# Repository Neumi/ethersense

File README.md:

# ethersense
Open source Ethernet connected multi-sensor.

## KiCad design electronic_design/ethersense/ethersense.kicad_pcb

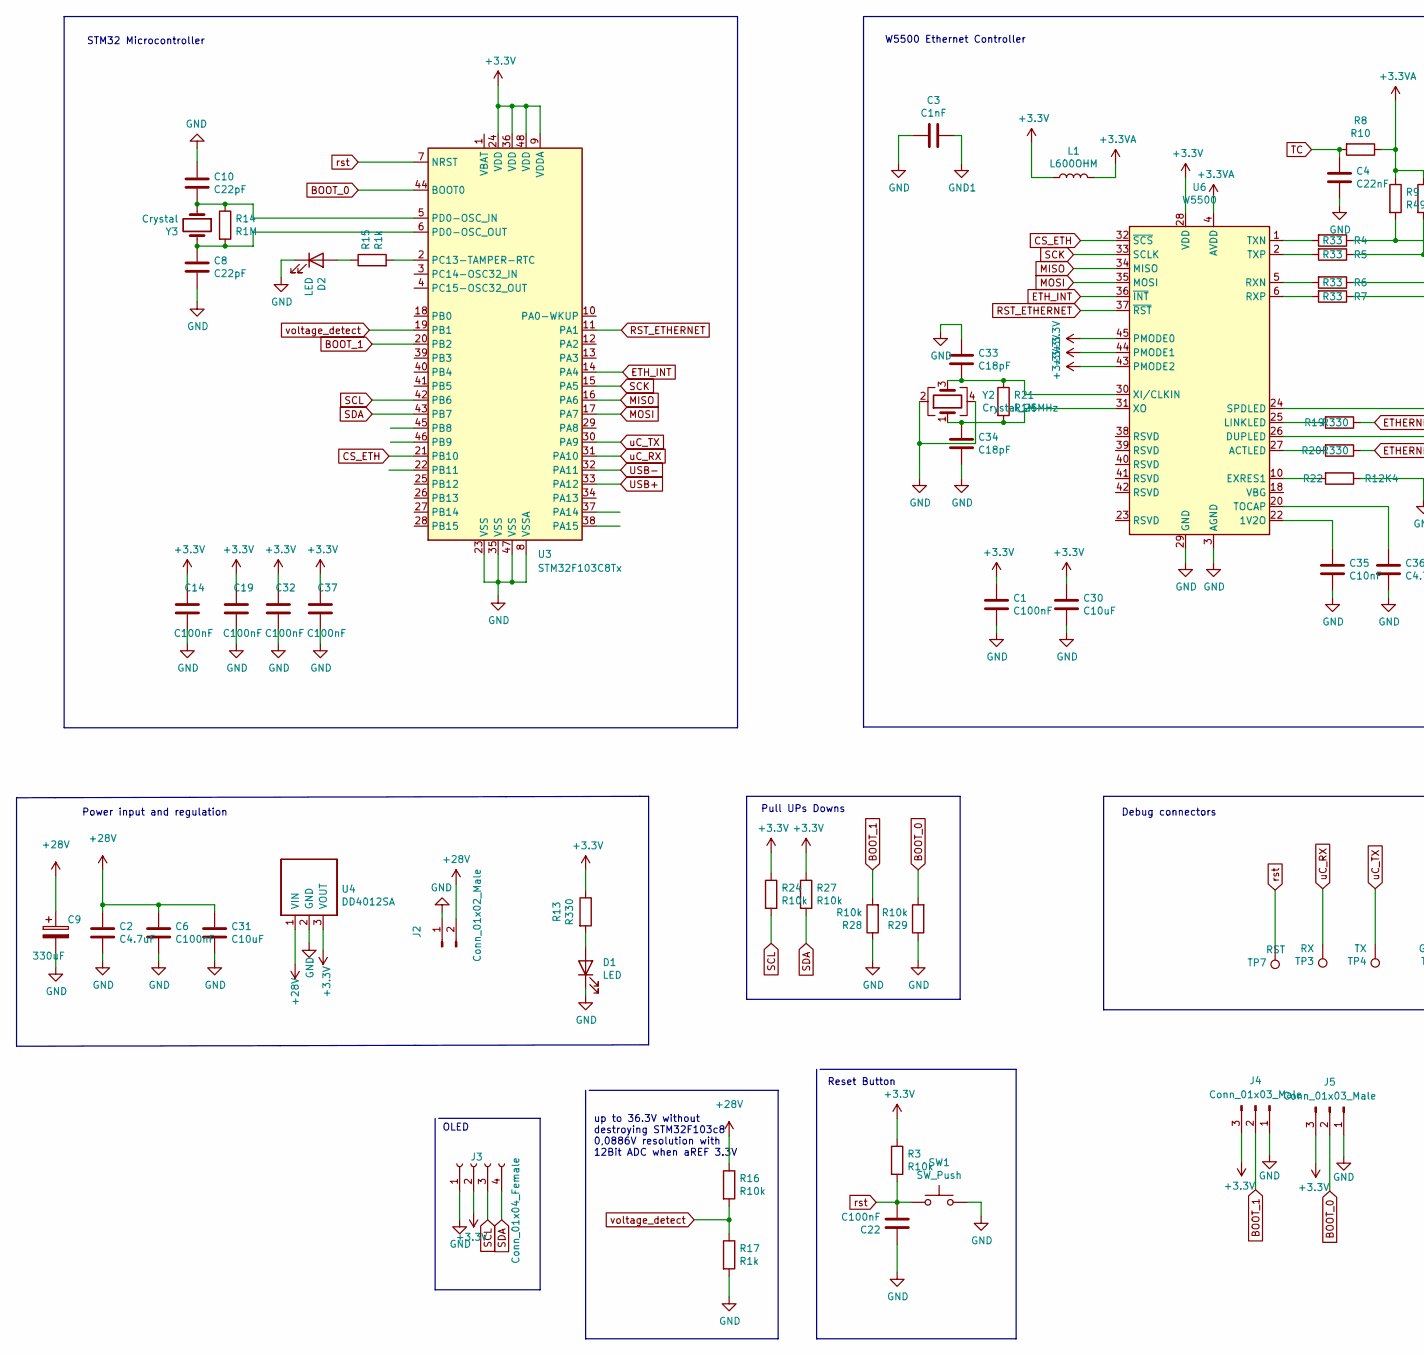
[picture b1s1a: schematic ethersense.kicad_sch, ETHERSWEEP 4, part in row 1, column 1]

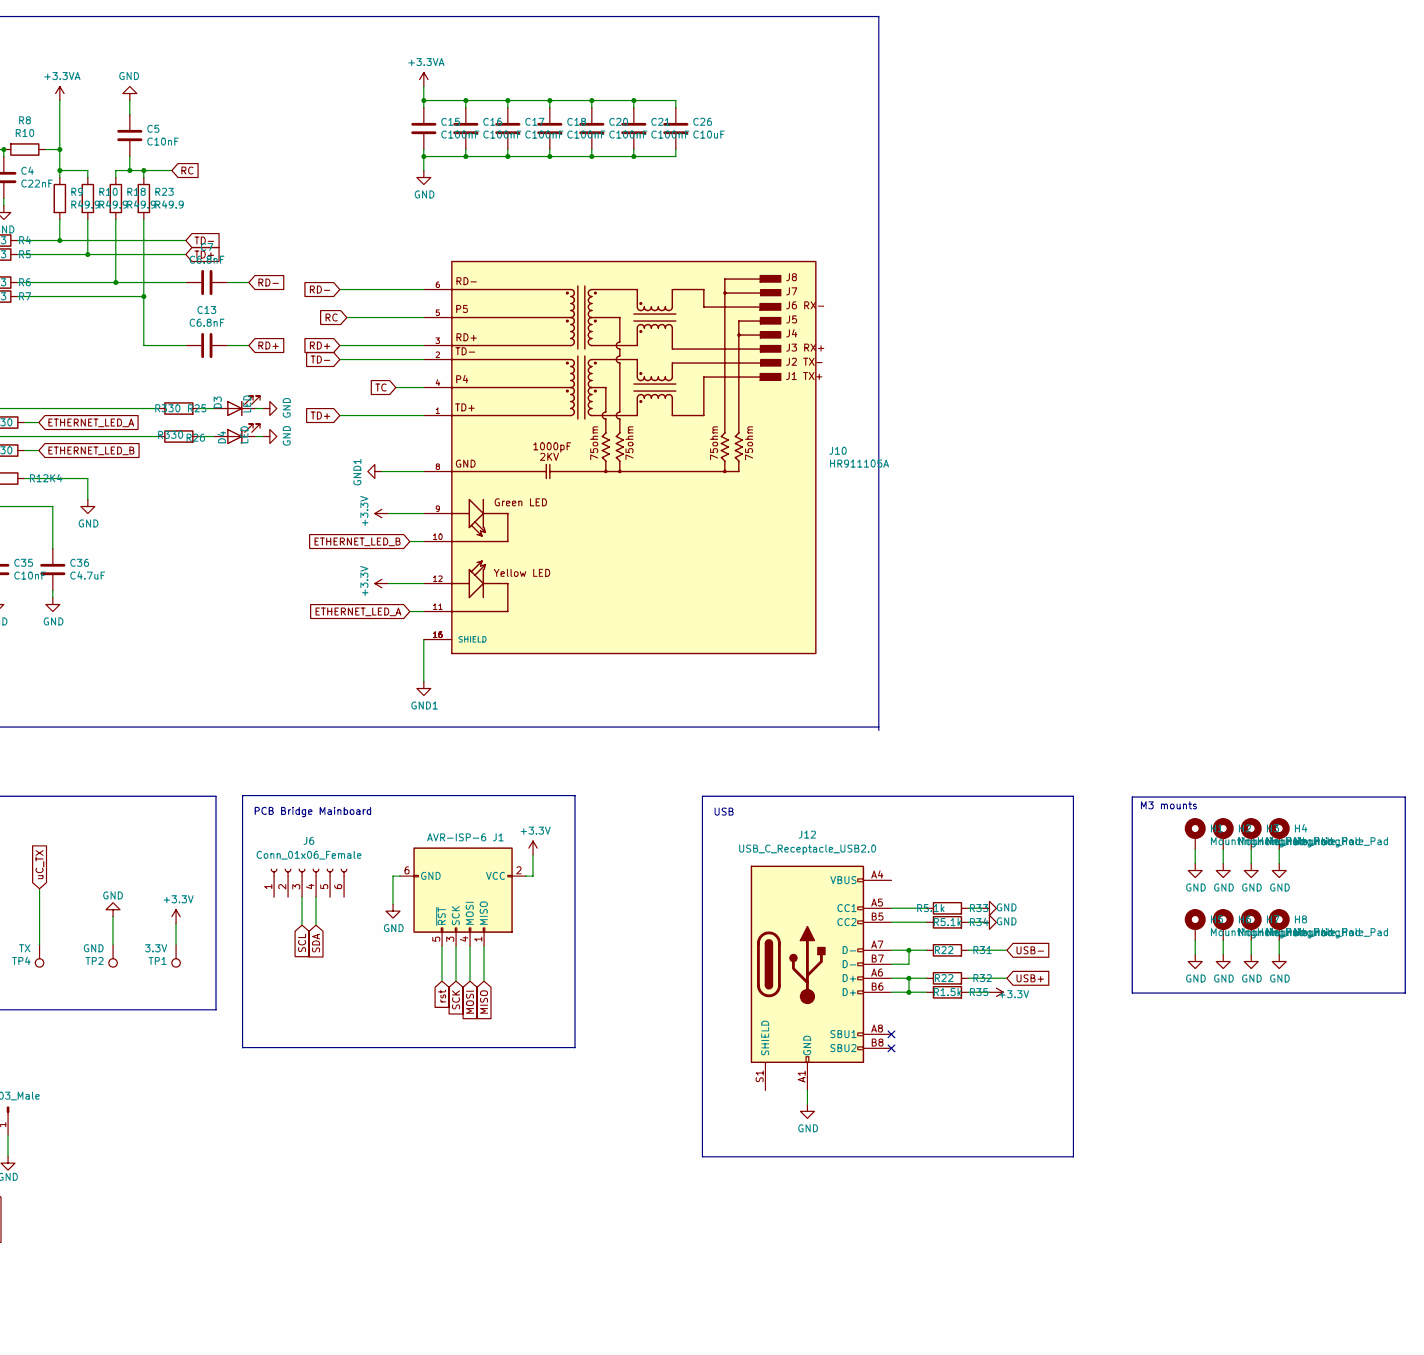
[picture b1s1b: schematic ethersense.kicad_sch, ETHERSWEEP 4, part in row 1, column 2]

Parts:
C1, C6: C100nF; C_0603_1608Metric; LCSC C14663
C2: C4.7uF; C_1206_3216Metric; LCSC C29823
C3: C1nF; C_1206_3216Metric; LCSC C35216
C4: C22nF; C_0603_1608Metric; LCSC C21122
C5: C10nF; C_0603_1608Metric; LCSC C57112
C7, C13: C6.8nF; C_0402_1005Metric; LCSC C1542
C8, C10: C22pF; C_0402_1005Metric; LCSC C1555
C9: 330uF; CP_Elec_10x10; LCSC C249985
C14, C15, C16, C17, C18, C19, C20, C21, C22, C32, C37: C100nF; C_0402_1005Metric; LCSC C307331
C26, C30: C10uF; C_0805_2012Metric; LCSC C15850
C31: C10uF; C_1206_3216Metric; LCSC C13585
C33, C34: C18pF; C_0402_1005Metric; LCSC C1549
C35: C10nF; C_0402_1005Metric; LCSC C15195
C36: C4.7uF; C_0402_1005Metric; LCSC C23733
D1, D2: LED; LED_0603_1608Metric; LCSC C2286
D3, D4: LED; LED_0603_1608Metric; LCSC C2296
H1, H2, H3, H4, H5, H6, H7, H8: MountingHole_Pad; MountingHole_3.2mm_M3_Pad_Via
J1: AVR-ISP-6; IDC-Header_2x03_P2.54mm_Vertical
J2: Conn_01x02_Male; AMASS_XT30PW-M_1x02_P2.50mm_Horizontal; LCSC C431092
J3: Conn_01x04_Female; PinHeader_1x04_P2.54mm_Vertical
J4, J5: Conn_01x03_Male; PinHeader_1x03_P2.54mm_Vertical
J6: Conn_01x06_Female; PinHeader_1x06_P2.54mm_Vertical
J10: HR911105A; HANRUN_HR911105A; PARTREV A; LCSC C12074
J12: USB_C_Receptacle_USB2.0; USB_C_Receptacle_HRO_TYPE-C-31-M-12; LCSC C165948
L1: L600OHM; L_0805_2012Metric; LCSC C1017
R3, R16, R24, R27, R28, R29: R10k; R_0402_1005Metric; LCSC C25744
R4, R5, R6, R7: R33; R_0603_1608Metric; LCSC C23140
R8: R10; R_0603_1608Metric; LCSC C22859
R9, R10, R18, R23: R49.9; R_0603_1608Metric; LCSC C23185
R13, R19, R20, R25, R26: R330; R_0603_1608Metric; LCSC C23138
R14, R21: R1M; R_0402_1005Metric; LCSC C26083
R15: R1k; R_0603_1608Metric; LCSC C21190
R17: R1k; R_0402_1005Metric; LCSC C11702
R22: R12K4; R_0603_1608Metric; LCSC C234268
R31, R32: R22; R_0402_1005Metric; LCSC C25767
R33, R34: R5.1k; R_0402_1005Metric; LCSC C105872
R35: R1.5k; R_0402_1005Metric; LCSC C25867
SW1: SW_Push; SW_Push_SPST_NO_Alps_SKRK; LCSC C720477
TP1: 3.3V; TestPoint_Pad_D2.0mm
TP2: GND; TestPoint_Pad_D2.0mm
TP3: RX; TestPoint_Pad_D2.0mm
TP4: TX; TestPoint_Pad_D2.0mm
TP7: RST; TestPoint_Pad_D2.0mm
U3: STM32F103C8Tx; LQFP-48_7x7mm_P0.5mm; LCSC C8734
U4: DD4012SA; PinHeader_1x03_P2.54mm_Vertical
U6: W5500; LQFP-48_7x7mm_P0.5mm; LCSC C32843
Y2: Crystal_25MHz; Crystal_SMD_3225-4Pin_3.2x2.5mm; LCSC C9006
Y3: Crystal; Crystal_SMD_5032-2Pin_5.0x3.2mm; LCSC C115962

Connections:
+3.3VA: C15.1, C16.1, C17.1, C18.1, C20.1, C21.1, C26.1, L1.2, R8.1, R9.1, R10.1, U6.4 (AVDD), U6.8 (AVDD), U6.11 (AVDD), U6.15 (AVDD), U6.17 (AVDD), U6.21 (AVDD)
+3V3: C1.1, C14.1, C19.1, C30.1, C32.1, C37.1, J1.2 (VCC), J3.2, J4.3, J5.3, J10.9, J10.12, L1.1, R3.1, R13.1, R24.1, R27.1, R35.2, TP1.1, U3.9 (VDDA), U3.24 (VDD), U3.36 (VDD), U3.48 (VDD), U4.3 (VOUT), U6.28 (VDD), U6.43 (PMODE2), U6.44 (PMODE1), U6.45 (PMODE0)
+28V: C2.1, C6.1, C9.1, C31.1, J2.2, R16.1, U4.1 (VIN)
BOOT_0: J5.2, R29.2, U3.44 (BOOT0)
BOOT_1: J4.2, R28.2, U3.20 (PB2)
CS_ETH: U3.21 (PB10), U6.32 (~SCS)
ENDSTOP: J6.2
ESTOP: J6.1
ETHERNET_LED_A: J10.11, R19.1
ETHERNET_LED_B: J10.10, R20.1
ETH_INT: J6.6, U3.14 (PA4), U6.36 (~INT)
GND: C1.2, C2.2, C3.2, C4.1, C5.1, C6.2, C8.2, C9.2, C10.1, C14.2, C15.2, C16.2, C17.2, C18.2, C19.2, C20.2, C21.2, C22.1, C26.2, C30.2, C31.2, C32.2, C33.1, C34.2, C35.2, C36.2, C37.2, D1.1 (K), D2.1 (K), D3.1 (K), D4.1 (K), H1.1, H2.1, H3.1, H4.1, H5.1, H6.1, H7.1, H8.1, J1.6 (GND), J2.1, J3.1, J4.1, J5.1, J12.A1 (GND), J12.A12 (GND), J12.B1 (GND), J12.B12 (GND), R17.2, R22.1, R28.1, R29.1, R33.2, R34.2, SW1.2, TP2.1, U3.8 (VSSA), U3.23 (VSS), U3.35 (VSS), U3.47 (VSS), U4.2 (GND), U6.3 (AGND), U6.9 (AGND), U6.14 (AGND), U6.16 (AGND), U6.19 (AGND), U6.29 (GND), U6.48 (AGND), Y2.2, Y2.4
GND1: C3.1, J10.8, J10.15 (SHIELD), J10.16 (SHIELD)
MISO: J1.1 (MISO), U3.16 (PA6), U6.34 (MISO)
MOSI: J1.4 (MOSI), U3.17 (PA7), U6.35 (MOSI)
unnamed: C7.2, R6.1, R18.2
unnamed: C8.1, R14.2, U3.6 (PD0-OSC_OUT), Y3.2
unnamed: C10.2, R14.1, U3.5 (PD0-OSC_IN), Y3.1
unnamed: C13.2, R7.1, R23.2
unnamed: C33.2, R21.1, U6.30 (XI/CLKIN), Y2.3
unnamed: C34.1, R21.2, U6.31 (XO), Y2.1
unnamed: C35.1, U6.22 (1V2O)
unnamed: C36.1, U6.20 (TOCAP)
unnamed: D1.2 (A), R13.2
unnamed: D2.2 (A), R15.1
unnamed: D3.2 (A), R25.2
unnamed: D4.2 (A), R26.2
unnamed: J12.A4 (VBUS), J12.A9 (VBUS), J12.B4 (VBUS), J12.B9 (VBUS)
unnamed: J12.A5 (CC1), R33.1
unnamed: J12.A6 (D+), J12.B6 (D+), R32.1, R35.1
unnamed: J12.A7 (D-), J12.B7 (D-), R31.1
unnamed: J12.B5 (CC2), R34.1
unnamed: R4.2, U6.1 (TXN)
unnamed: R5.2, U6.2 (TXP)
unnamed: R6.2, U6.5 (RXN)
unnamed: R7.2, U6.6 (RXP)
unnamed: R15.2, U3.2 (PC13-TAMPER-RTC)
unnamed: R19.2, U6.25 (LINKLED)
unnamed: R20.2, U6.27 (ACTLED)
unnamed: R22.2, U6.10 (EXRES1)
unnamed: R25.1, U6.24 (SPDLED)
unnamed: R26.1, U6.26 (DUPLED)
RC: C5.2, J10.5, R18.1, R23.1
RD+: C13.1, J10.3
RD-: C7.1, J10.6
RST_ETHERNET: J6.5, U3.11 (PA1), U6.37 (~RST)
SCK: J1.3 (SCK), U3.15 (PA5), U6.33 (SCLK)
SCL: J3.3, J6.3, R24.2, U3.42 (PB6)
SDA: J3.4, J6.4, R27.2, U3.43 (PB7)
TC: C4.2, J10.4, R8.2
TD+: J10.1, R5.1, R10.2
TD-: J10.2, R4.1, R9.2
USB+: R32.2, U3.33 (PA12)
USB-: R31.2, U3.32 (PA11)
rst: C22.2, J1.5 (~RST), R3.2, SW1.1, TP7.1, U3.7 (NRST)
uC_RX: TP3.1, U3.31 (PA10)
uC_TX: TP4.1, U3.30 (PA9)
voltage_detect: R16.2, R17.1, U3.19 (PB1)

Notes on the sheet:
USB
W5500 Ethernet Controller
M3 mounts
OLED
Power input and regulation
Debug connectors
Pull UPs Downs
STM32 Microcontroller
up to 36.3V without destroying STM32F103c8 0,0886V resolution with 12Bit ADC when aREF 3.3V
Reset Button
PCB Bridge Mainboard

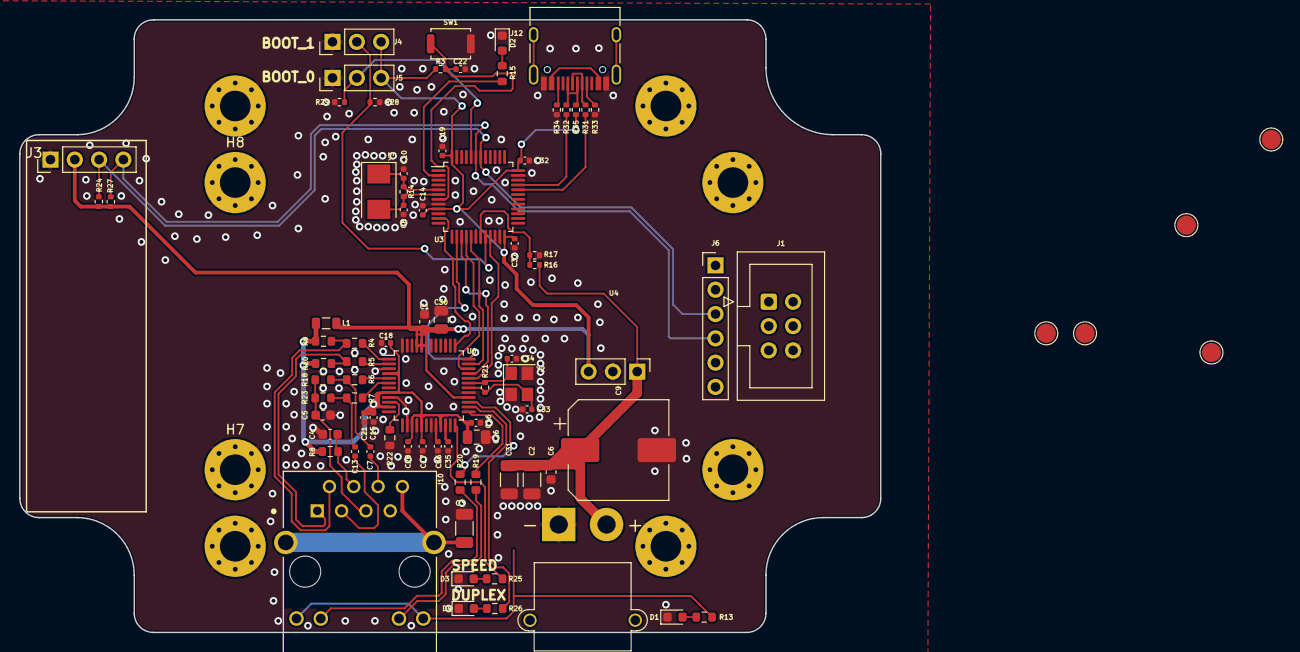
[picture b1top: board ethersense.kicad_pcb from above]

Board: 2 copper layers, 89.9 x 64.0 mm, 91 parts (0 on the bottom side), 56 nets.

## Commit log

2023-02-13 added electronics design init
